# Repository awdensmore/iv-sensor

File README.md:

# iv-sensor
A sensor for voltage and current measurements used in electrochemical impedance spectroscopy. Output is suitable for 3V logic level (DSPs)

###**Operation**
The purpose of this sensor is to accurately measure the current and voltage response of a battery excited by an EIS waveform. The current is measured using a transducer (U1) and passed directly to an output connected to the ADC of a DSP.

The voltage measurement is more complicated. Because the EIS signal is a ~20mV sine wave on top of a ~12V DC signal, the DC component must be removed and the AC component amplified before it is input to the ADC for digitization. This is accomplished in several steps:

1. **Determine DC component of voltage signal**: The battery voltage is measured on the low side of the transducer (I- @ U1). That signal is passed through a voltage divider (R1 / R2), after which it is passed to an external ADC via pin 2 of P1. The external DSP uses a software low-pass filter to remove the AC component, then passes the signal back to this PCB via pin 1 of P1. However, because the DSP only has PWM output (not a pure analog output), this signal needs a DAC. The DAC is built using F1 / F2, which act as a 4-pole programmable active filter. At this point the signal (FO @ pin 1 of F2) is DC and proportional to the original battery DC component, but not the same voltage. It is therefore amplified using OP1, and is now within a few mV of the original battery DC voltage (OP1-OUT @ pin 6 of OP1).
2. **Remove DC component**: The signal created by step 1 is then removed from the original signal (I-) via OP2 (OP2_OUT @ pin 6). We now have only the ~20mV AC signal.
3. **Amplification & offset**: The AC signal is amplified ~35x at OP-3, and then offset by 1.5V at OP-4 so that the signal is always positive. The final EIS voltage signal (Vo) is output to the DSP at pin 3 of P1.

**Component Values**

| Component | Value |
|----------|-------|
R1 | 21.92k
R2 | 5.57k
R3 | 82.2k
R4 | 4.64M
R5 | 4.7M
R6 | 50.9k
R7 | 15.9k
R8 | 4.57M
R9 | 4.66M
R10 | 51.0k
R11 | 984
R12 | 100.1k
R13 | 19.98k
R14 | 19.98k
R15 | 100.4k
R16 | 62.3k
R17 | 62.2k
R18 | 62.1k
R19 | 62.3k
R20 | 100.0k
R21 | 2.99k
R22 | 1k
R23 | 100.3k
R24 | 22k
R25 | 21.87k
R26 | TBD
R27 | TBD
R28 | TBD
C1 - C2 | 470uF
C3 - C16 | 0.1uF

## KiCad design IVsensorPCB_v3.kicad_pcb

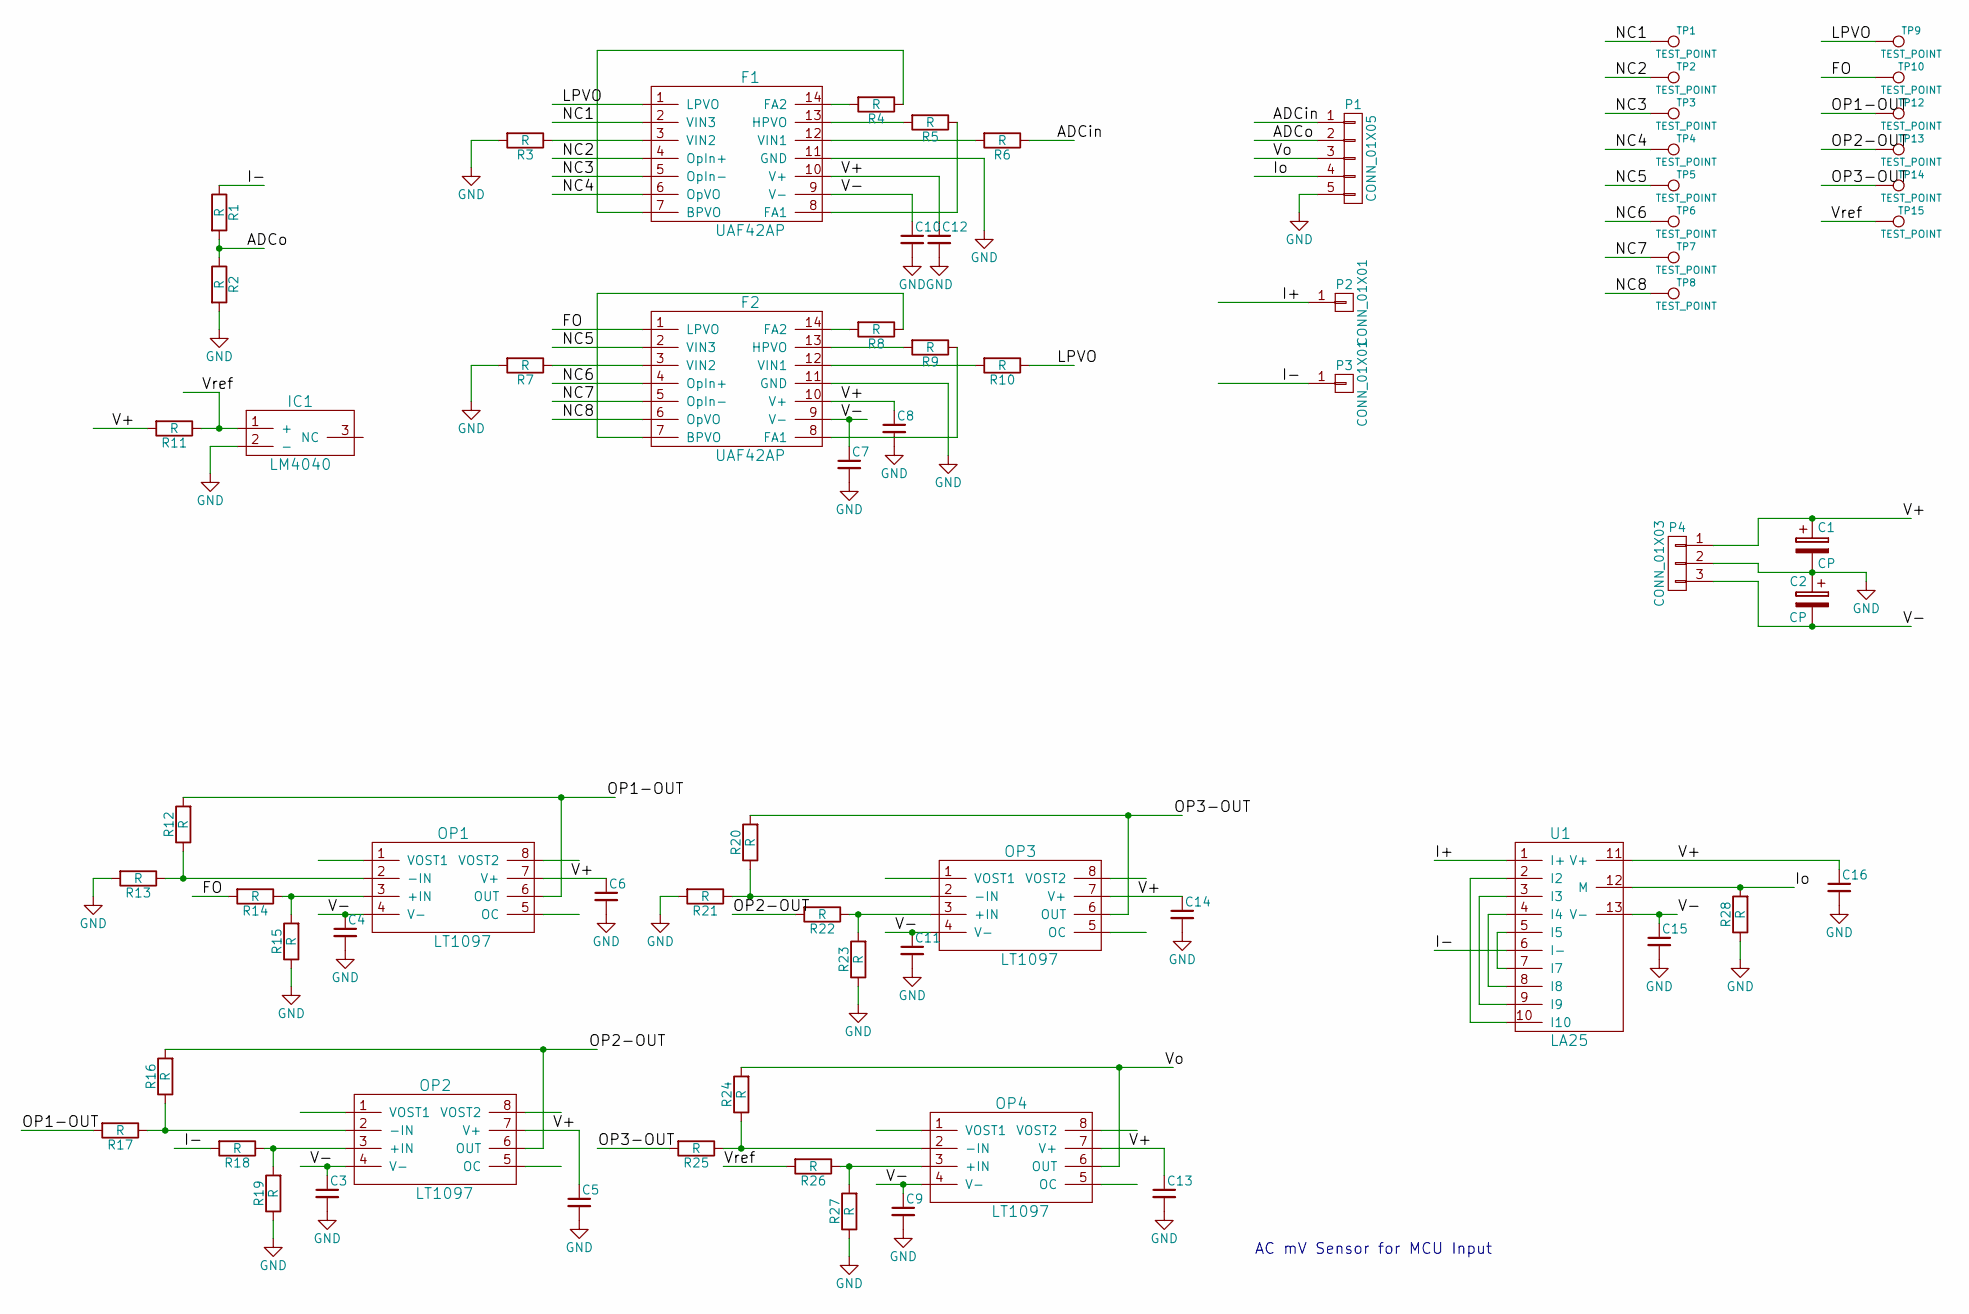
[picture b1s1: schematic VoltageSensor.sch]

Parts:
C1, C2: CP; Elko_vert_11.5x8mm_RM3.5
C3, C4, C5, C6, C7, C8, C9, C10, C11, C12, C13, C14, C15, C16: C_Small; C_Disc_D3_P2.5
F1, F2: UAF42AP; DIP-14_W7.62mm_LongPads
IC1: LM4040; SOT-23
OP1, OP2, OP3, OP4: LT1097; DIP-8_W7.62mm_LongPads
P1: CONN_01X05; Pin_Header_Straight_1x05
P2, P3: CONN_01X01; Pin_Header_Straight_1x01
P4: CONN_01X03; Pin_Header_Straight_1x03
R1, R2, R3, R4, R5, R6, R7, R8, R9, R10, R11, R12, R13, R14, R15, R16, R17, R18, R19, R20, R21, R22, R23, R24, R25, R26, R27, R28: R; Resistor_Horizontal_RM10mm
TP1, TP2, TP3, TP4, TP5, TP6, TP7, TP8, TP9, TP10, TP12, TP13, TP14, TP15: TEST_POINT; Measurement_Point_Round-TH_Small
U1: LA25

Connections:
/ADCin: P1.1, R6.1
/ADCo: P1.2, R1.2, R2.1
/FO: F2.1 (LPVO), R14.2, TP10.1
/I+: P2.1, U1.1 (I+)
/I-: P3.1, R1.1, R18.2, U1.6 (I-)
/Io: P1.4, R28.2, U1.12 (M)
/LPVO: F1.1 (LPVO), R10.1, TP9.1
/NC1: F1.2 (VIN3), TP1.1
/NC2: F1.4 (OpIn+), TP2.1
/NC3: F1.5 (OpIn-), TP3.1
/NC4: F1.6 (OpVO), TP4.1
/NC5: F2.2 (VIN3), TP5.1
/NC6: F2.4 (OpIn+), TP6.1
/NC7: F2.5 (OpIn-), TP7.1
/NC8: F2.6 (OpVO), TP8.1
/OP1-OUT: OP1.6 (OUT), R12.2, R17.2, TP12.1
/OP2-OUT: OP2.6 (OUT), R16.2, R22.2, TP13.1
/OP3-OUT: OP3.6 (OUT), R20.2, R25.2, TP14.1
/V+: C1.1, C5.1, C6.1, C8.1, C12.1, C13.1, C14.1, C16.1, F1.10 (V+), F2.10 (V+), OP1.7 (V+), OP2.7 (V+), OP3.7 (V+), OP4.7 (V+), P4.1, R11.2, U1.11 (V+)
/V-: C2.2, C3.1, C4.1, C7.1, C9.1, C10.1, C11.1, C15.1, F1.9 (V-), F2.9 (V-), OP1.4 (V-), OP2.4 (V-), OP3.4 (V-), OP4.4 (V-), P4.3, U1.13 (V-)
/Vo: OP4.6 (OUT), P1.3, R24.2
/Vref: IC1.1 (+), R11.1, R26.2, TP15.1
GND: C1.2, C2.1, C3.2, C4.2, C5.2, C6.2, C7.2, C8.2, C9.2, C10.2, C11.2, C12.2, C13.2, C14.2, C15.2, C16.2, F1.11 (GND), F2.11 (GND), IC1.2 (-), P1.5, P4.2, R2.2, R3.2, R7.2, R13.2, R15.1, R19.1, R21.2, R23.1, R27.1, R28.1
unnamed: F1.3 (VIN2), R3.1
unnamed: F1.7 (BPVO), R4.1
unnamed: F1.8 (FA1), R5.1
unnamed: F1.12 (VIN1), R6.2
unnamed: F1.13 (HPVO), R5.2
unnamed: F1.14 (FA2), R4.2
unnamed: F2.3 (VIN2), R7.1
unnamed: F2.7 (BPVO), R8.1
unnamed: F2.8 (FA1), R9.1
unnamed: F2.12 (VIN1), R10.2
unnamed: F2.13 (HPVO), R9.2
unnamed: F2.14 (FA2), R8.2
unnamed: OP1.2 (-IN), R12.1, R13.1
unnamed: OP1.3 (+IN), R14.1, R15.2
unnamed: OP2.2 (-IN), R16.1, R17.1
unnamed: OP2.3 (+IN), R18.1, R19.2
unnamed: OP3.2 (-IN), R20.1, R21.1
unnamed: OP3.3 (+IN), R22.1, R23.2
unnamed: OP4.2 (-IN), R24.1, R25.1
unnamed: OP4.3 (+IN), R26.1, R27.2
unnamed: U1.3 (I3), U1.9 (I9)
unnamed: U1.4 (I4), U1.8 (I8)
unnamed: U1.5 (I5), U1.7 (I7)
unnamed: U1.2 (I2), U1.10 (I10)

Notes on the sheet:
AC mV Sensor for MCU Input

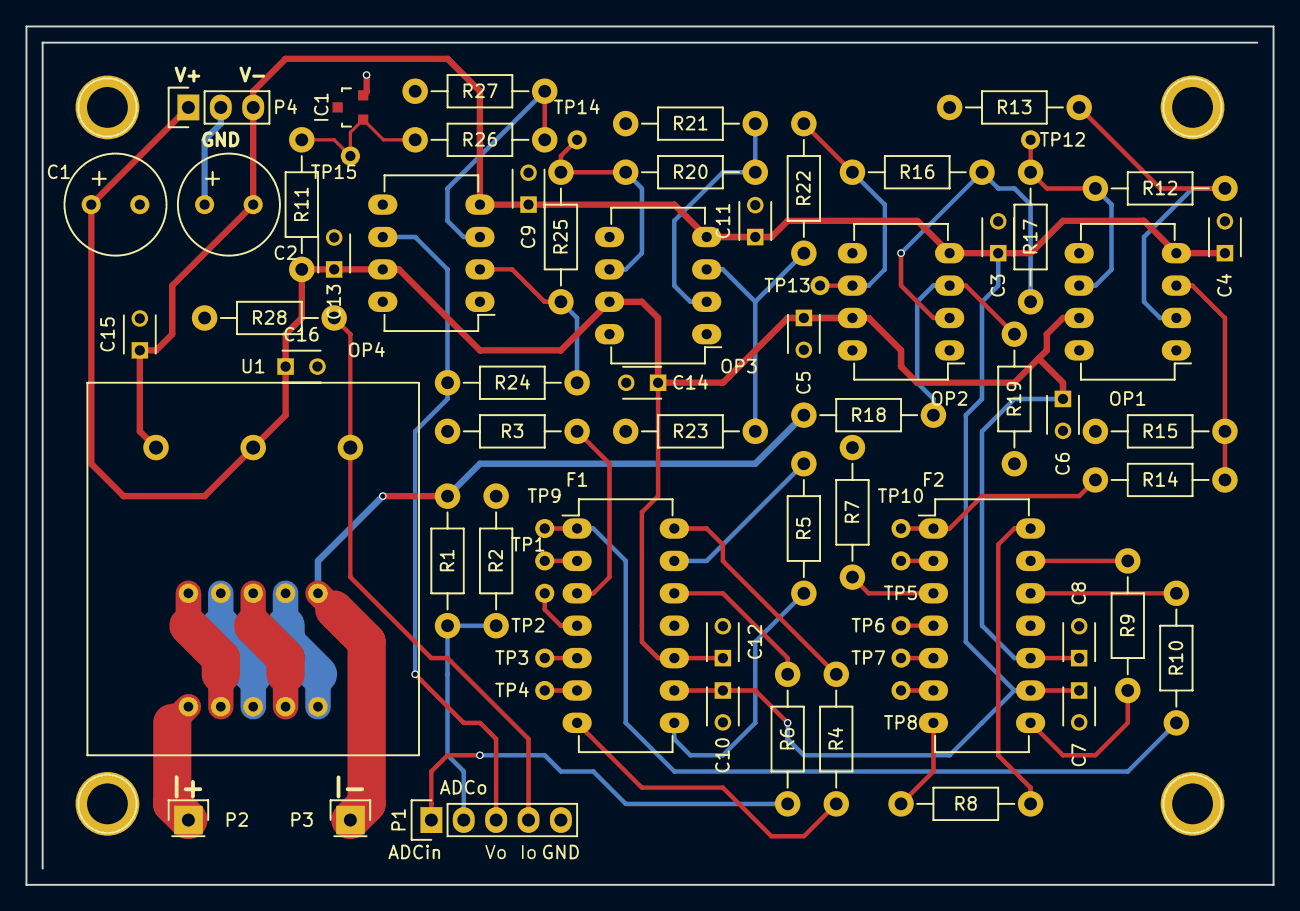
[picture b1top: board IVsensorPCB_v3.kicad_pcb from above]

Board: 2 copper layers, 97.8 x 67.3 mm, 70 parts (0 on the bottom side), 47 nets.

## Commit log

2015-11-18 added existing files
2015-11-26 added operation diagram
